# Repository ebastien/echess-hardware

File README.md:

# e-Chess project

Models for 3D printing and PCB layouts.

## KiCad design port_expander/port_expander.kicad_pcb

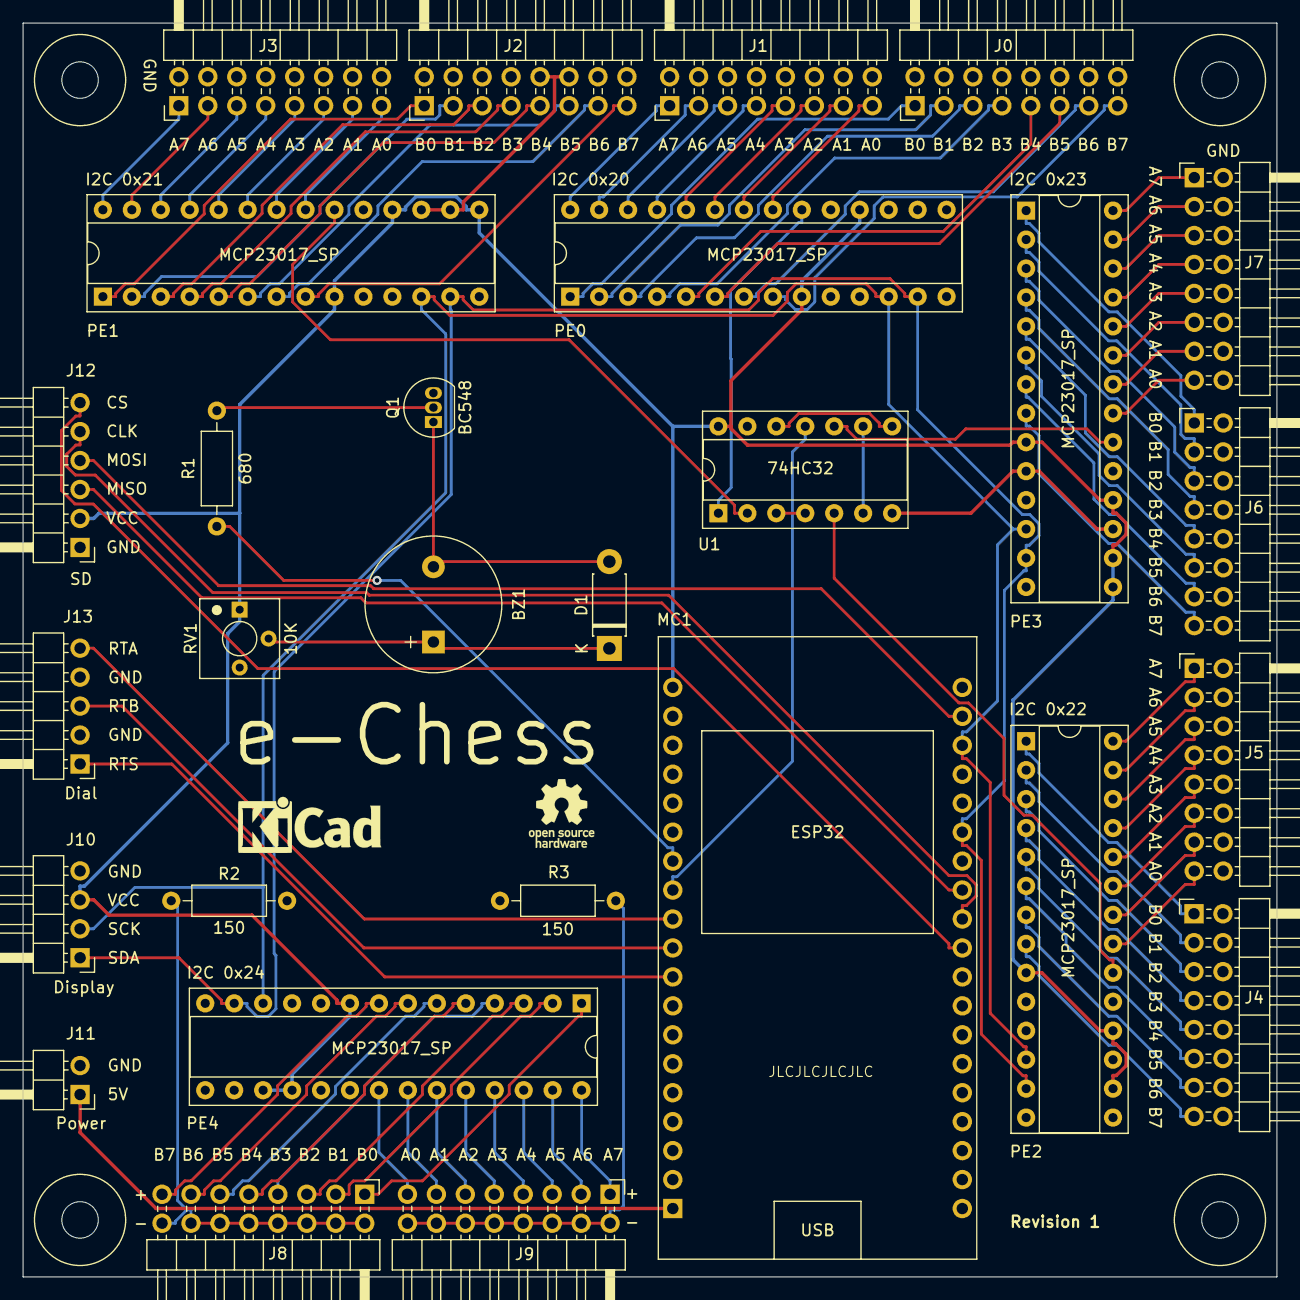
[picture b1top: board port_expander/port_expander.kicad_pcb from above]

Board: 2 copper layers, 110.0 x 110.0 mm, 33 parts (0 on the bottom side), 106 nets.

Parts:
BZ1: Buzzer; PassiveBuzzer_D12_H8.2_P6.6
D1: 1N4007; D_DO-41_SOD81_P7.62mm_Horizontal
J0, J1, J2, J3, J4, J5, J6, J7, J8, J9: Conn_02x08_Male; PinHeader_2x08_P2.54mm_Horizontal
J10: Display; PinHeader_1x04_P2.54mm_Horizontal
J11: Power; PinHeader_1x02_P2.54mm_Horizontal
J12: SD; PinHeader_1x06_P2.54mm_Horizontal
J13: Dial; PinHeader_1x05_P2.54mm_Horizontal
L0: KiCad-Logo_5mm_SilkScreen
MC1: ESP32_DevKitC
MH1, MH2, MH3, MH4: MountingHole_3.2mm_M3
PE0, PE1, PE2, PE3, PE4: MCP23017_SP; DIP-28_W7.62mm_Socket
Q1: BC548; TO-92_Inline
R1: 680; R_Axial_DIN0207_L6.3mm_D2.5mm_P10.16mm_Horizontal
R2, R3: 150; R_Axial_DIN0207_L6.3mm_D2.5mm_P10.16mm_Horizontal
RV1: 10K; BOURNS-3362P_pot
U1: 74HC32; DIP-14_W7.62mm_Socket

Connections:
+3V3: J10.3, J12.2, MC1.19, PE0.9, PE0.18, PE1.9, PE1.15, PE1.18, PE2.9, PE2.16, PE2.18, PE3.9, PE3.15, PE3.16, PE3.18, PE4.9, PE4.17, PE4.18, RV1.1, U1.14
/5V: J11.1, MC1.1
/BUZ: MC1.13, R1.2
/E0A0: J1.15, PE0.21
/E0A1: J1.13, PE0.22
/E0A2: J1.11, PE0.23
/E0A3: J1.9, PE0.24
/E0A4: J1.7, PE0.25
/E0A5: J1.5, PE0.26
/E0A6: J1.3, PE0.27
/E0A7: J1.1, PE0.28
/E0B0: J0.1, PE0.1
/E0B1: J0.3, PE0.2
/E0B2: J0.5, PE0.3
/E0B3: J0.7, PE0.4
/E0B4: J0.9, PE0.5
/E0B5: J0.11, PE0.6
/E0B6: J0.13, PE0.7
/E0B7: J0.15, PE0.8
/E1A0: J3.15, PE1.21
/E1A1: J3.13, PE1.22
/E1A2: J3.11, PE1.23
/E1A3: J3.9, PE1.24
/E1A4: J3.7, PE1.25
/E1A5: J3.5, PE1.26
/E1A6: J3.3, PE1.27
/E1A7: J3.1, PE1.28
/E1B0: J2.1, PE1.1
/E1B1: J2.3, PE1.2
/E1B2: J2.5, PE1.3
/E1B3: J2.7, PE1.4
/E1B4: J2.9, PE1.5
/E1B5: J2.11, PE1.6
/E1B6: J2.13, PE1.7
/E1B7: J2.15, PE1.8
/E2A0: J5.15, PE2.21
/E2A1: J5.13, PE2.22
/E2A2: J5.11, PE2.23
/E2A3: J5.9, PE2.24
/E2A4: J5.7, PE2.25
/E2A5: J5.5, PE2.26
/E2A6: J5.3, PE2.27
/E2A7: J5.1, PE2.28
/E2B0: J4.1, PE2.1
/E2B1: J4.3, PE2.2
/E2B2: J4.5, PE2.3
/E2B3: J4.7, PE2.4
/E2B4: J4.9, PE2.5
/E2B5: J4.11, PE2.6
/E2B6: J4.13, PE2.7
/E2B7: J4.15, PE2.8
/E3A0: J7.15, PE3.21
/E3A1: J7.13, PE3.22
/E3A2: J7.11, PE3.23
/E3A3: J7.9, PE3.24
/E3A4: J7.7, PE3.25
/E3A5: J7.5, PE3.26
/E3A6: J7.3, PE3.27
/E3A7: J7.1, PE3.28
/E3B0: J6.1, PE3.1
/E3B1: J6.3, PE3.2
/E3B2: J6.5, PE3.3
/E3B3: J6.7, PE3.4
/E3B4: J6.9, PE3.5
/E3B5: J6.11, PE3.6
/E3B6: J6.13, PE3.7
/E3B7: J6.15, PE3.8
/E4A0: J9.15, PE4.21
/E4A1: J9.13, PE4.22
/E4A2: J9.11, PE4.23
/E4A3: J9.9, PE4.24
/E4A4: J9.7, PE4.25
/E4A5: J9.5, PE4.26
/E4A6: J9.3, PE4.27
/E4A7: J9.1, PE4.28
/E4B0: J8.1, PE4.1
/E4B1: J8.3, PE4.2
/E4B2: J8.5, PE4.3
/E4B3: J8.7, PE4.4
/E4B4: J8.9, PE4.5
/E4B5: J8.11, PE4.6
/E4B6: J8.13, PE4.7
/E4B7: J8.15, PE4.8
/INT: MC1.12, U1.11
/INT0: PE0.20, U1.1
/INT1: PE1.20, U1.2
/INT2: PE2.20, U1.5
/INT3: PE3.20, U1.10
/MISO: J12.3, MC1.27
/MOSI: J12.4, MC1.21
/RTA: J13.5, MC1.11
/RTB: J13.3, MC1.10
/RTS: J13.1, MC1.9
/SCK: J10.2, MC1.22, PE0.12, PE1.12, PE2.12, PE3.12, PE4.12
/SDA: J10.1, MC1.25, PE0.13, PE1.13, PE2.13, PE3.13, PE4.13
/SPICLK: J12.5, MC1.28
/SPICS: J12.6, MC1.29
GND: J0.2, J0.4, J0.6, J0.8, J0.10, J0.12, J0.14, J0.16, J1.2, J1.4, J1.6, J1.8, J1.10, J1.12, J1.14, J1.16, J2.2, J2.4, J2.6, J2.8, J2.10, J2.12, J2.14, J2.16, J3.2, J3.4, J3.6, J3.8, J3.10, J3.12, J3.14, J3.16, J4.2, J4.4, J4.6, J4.8, J4.10, J4.12, J4.14, J4.16, J5.2, J5.4, J5.6, J5.8, J5.10, J5.12, J5.14, J5.16, J6.2, J6.4, J6.6, J6.8, J6.10, J6.12, J6.14, J6.16, J7.2, J7.4, J7.6, J7.8, J7.10, J7.12, J7.14, J7.16, J10.4, J11.2, J12.1, J13.2, J13.4, MC1.6, MC1.20, MC1.26, PE0.10, PE0.15, PE0.16, PE0.17, PE1.10, PE1.16, PE1.17, PE2.10, PE2.15, PE2.17, PE3.10, PE3.17, PE4.10, PE4.15, PE4.16, Q1.3, R2.2, R3.2, U1.7, U1.13
unnamed: BZ1.1, D1.1, RV1.2
unnamed: BZ1.2, D1.2, Q1.1
unnamed: J8.2, J8.4, J8.6, J8.8, J8.10, J8.12, J8.14, J8.16, R2.1
unnamed: J9.2, J9.4, J9.6, J9.8, J9.10, J9.12, J9.14, J9.16, R3.1
unnamed: Q1.2, R1.1
unnamed: U1.3, U1.4
unnamed: U1.6, U1.9
unnamed: U1.8, U1.12

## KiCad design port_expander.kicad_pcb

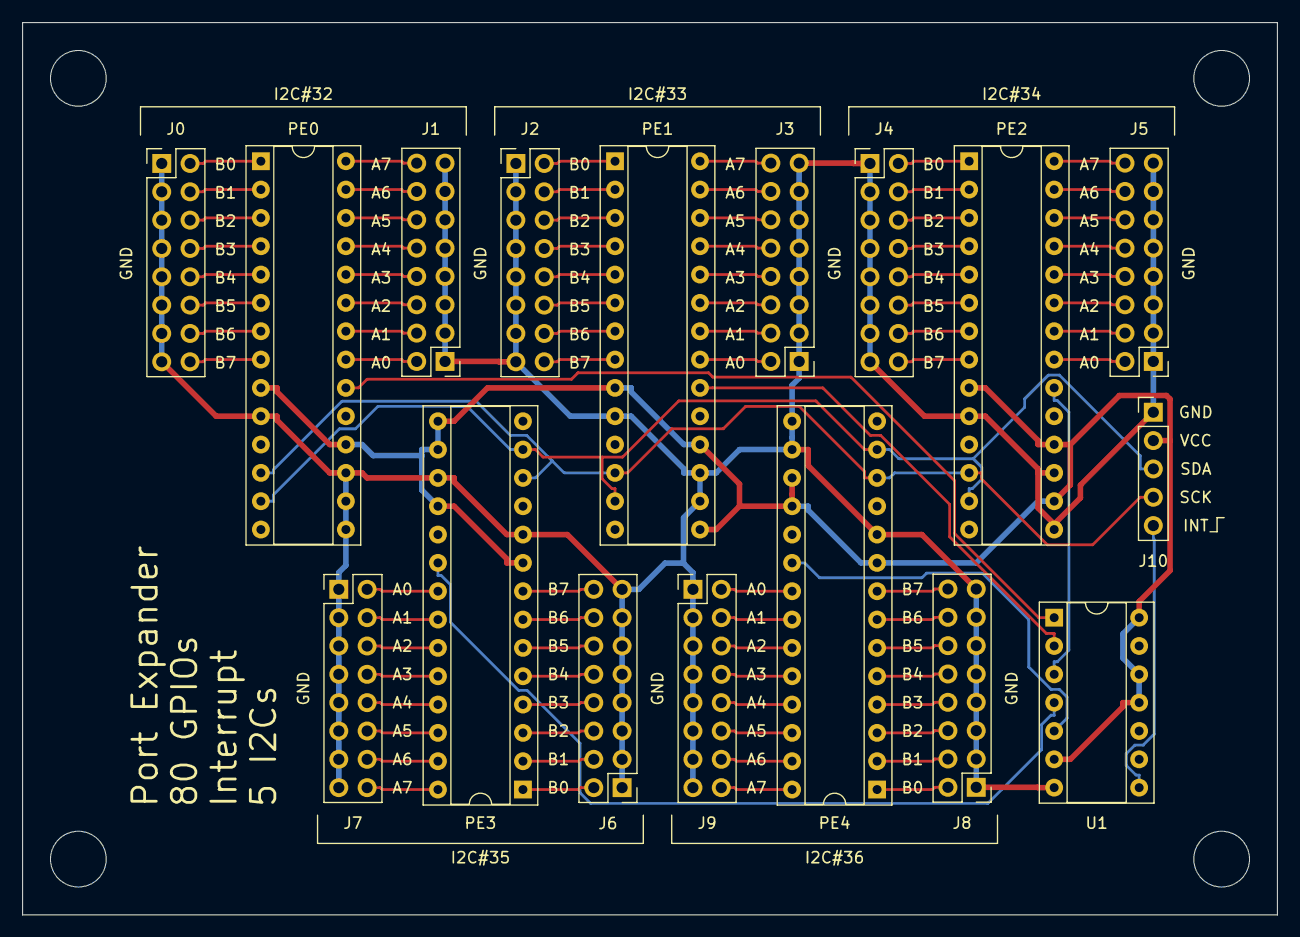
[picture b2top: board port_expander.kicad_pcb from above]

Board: 2 copper layers, 112.5 x 80.0 mm, 17 parts (0 on the bottom side), 90 nets.

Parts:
J0, J1, J2, J3, J4, J5, J6, J7, J8, J9: Conn_02x08_Male; PinHeader_2x08_P2.54mm_Vertical
J10: Conn_01x05_Male; PinHeader_1x05_P2.54mm_Vertical
PE0, PE1, PE2, PE3, PE4: MCP23017_SP; DIP-28_W7.62mm_Socket
U1: 74LS30; DIP-14_W7.62mm_Socket

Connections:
+3V3: J10.2, PE0.9, PE0.18, PE1.9, PE1.15, PE1.18, PE2.9, PE2.16, PE2.18, PE3.9, PE3.15, PE3.16, PE3.18, PE4.9, PE4.17, PE4.18, U1.6, U1.11, U1.12, U1.14
/INT: J10.5, U1.8
/INT0: PE0.20, U1.1
/INT1: PE1.20, U1.2
/INT2: PE2.20, U1.3
/INT3: PE3.20, U1.4
/INT4: PE4.20, U1.5
/SCK: J10.4, PE0.12, PE1.12, PE2.12, PE3.12, PE4.12
/SDA: J10.3, PE0.13, PE1.13, PE2.13, PE3.13, PE4.13
GND: J0.1, J0.3, J0.5, J0.7, J0.9, J0.11, J0.13, J0.15, J1.1, J1.3, J1.5, J1.7, J1.9, J1.11, J1.13, J1.15, J2.1, J2.3, J2.5, J2.7, J2.9, J2.11, J2.13, J2.15, J3.1, J3.3, J3.5, J3.7, J3.9, J3.11, J3.13, J3.15, J4.1, J4.3, J4.5, J4.7, J4.9, J4.11, J4.13, J4.15, J5.1, J5.3, J5.5, J5.7, J5.9, J5.11, J5.13, J5.15, J6.1, J6.3, J6.5, J6.7, J6.9, J6.11, J6.13, J6.15, J7.1, J7.3, J7.5, J7.7, J7.9, J7.11, J7.13, J7.15, J8.1, J8.3, J8.5, J8.7, J8.9, J8.11, J8.13, J8.15, J9.1, J9.3, J9.5, J9.7, J9.9, J9.11, J9.13, J9.15, J10.1, PE0.10, PE0.15, PE0.16, PE0.17, PE1.10, PE1.16, PE1.17, PE2.10, PE2.15, PE2.17, PE3.10, PE3.17, PE4.10, PE4.15, PE4.16, U1.7
unnamed: J0.2, PE0.1
unnamed: J0.4, PE0.2
unnamed: J0.6, PE0.3
unnamed: J0.8, PE0.4
unnamed: J0.10, PE0.5
unnamed: J0.12, PE0.6
unnamed: J0.14, PE0.7
unnamed: J0.16, PE0.8
unnamed: J1.2, PE0.21
unnamed: J1.4, PE0.22
unnamed: J1.6, PE0.23
unnamed: J1.8, PE0.24
unnamed: J1.10, PE0.25
unnamed: J1.12, PE0.26
unnamed: J1.14, PE0.27
unnamed: J1.16, PE0.28
unnamed: J2.2, PE1.1
unnamed: J2.4, PE1.2
unnamed: J2.6, PE1.3
unnamed: J2.8, PE1.4
unnamed: J2.10, PE1.5
unnamed: J2.12, PE1.6
unnamed: J2.14, PE1.7
unnamed: J2.16, PE1.8
unnamed: J3.2, PE1.21
unnamed: J3.4, PE1.22
unnamed: J3.6, PE1.23
unnamed: J3.8, PE1.24
unnamed: J3.10, PE1.25
unnamed: J3.12, PE1.26
unnamed: J3.14, PE1.27
unnamed: J3.16, PE1.28
unnamed: J4.2, PE2.1
unnamed: J4.4, PE2.2
unnamed: J4.6, PE2.3
unnamed: J4.8, PE2.4
unnamed: J4.10, PE2.5
unnamed: J4.12, PE2.6
unnamed: J4.14, PE2.7
unnamed: J4.16, PE2.8
unnamed: J5.2, PE2.21
unnamed: J5.4, PE2.22
unnamed: J5.6, PE2.23
unnamed: J5.8, PE2.24
unnamed: J5.10, PE2.25
unnamed: J5.12, PE2.26
unnamed: J5.14, PE2.27
unnamed: J5.16, PE2.28
unnamed: J6.2, PE3.1
unnamed: J6.4, PE3.2
unnamed: J6.6, PE3.3
unnamed: J6.8, PE3.4
unnamed: J6.10, PE3.5
unnamed: J6.12, PE3.6
unnamed: J6.14, PE3.7
unnamed: J6.16, PE3.8
unnamed: J7.2, PE3.21
unnamed: J7.4, PE3.22
unnamed: J7.6, PE3.23
unnamed: J7.8, PE3.24
unnamed: J7.10, PE3.25
unnamed: J7.12, PE3.26
unnamed: J7.14, PE3.27
unnamed: J7.16, PE3.28
unnamed: J8.2, PE4.1
unnamed: J8.4, PE4.2
unnamed: J8.6, PE4.3
unnamed: J8.8, PE4.4
unnamed: J8.10, PE4.5
unnamed: J8.12, PE4.6
unnamed: J8.14, PE4.7
unnamed: J8.16, PE4.8
unnamed: J9.2, PE4.21
unnamed: J9.4, PE4.22
unnamed: J9.6, PE4.23
unnamed: J9.8, PE4.24
unnamed: J9.10, PE4.25
unnamed: J9.12, PE4.26
unnamed: J9.14, PE4.27
unnamed: J9.16, PE4.28

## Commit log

2021-01-04 chore: first schematic iteration
2021-01-07 2x8 headers
2021-01-07 first pcb iteration
2021-01-08 smaller pcb
2021-01-09 esp32 library
2021-01-10 change files layout
2022-11-20 board sensor array
2022-11-20 spacer
2022-11-20 first spacer print and reed fix pcb order
2022-11-20 port expander with MCU
2022-11-20 compact port expander layout
2022-11-20 case and pcb
2022-11-20 complete main board
2022-11-20 main board routing
2022-11-20 refined routing
2022-11-20 pcb manufacturing
2022-11-20 display case
2022-11-20 diode on buzzer
2022-11-20 display and m3 spacer
2022-11-20 magnet holders and display improvement
2022-11-20 Add README.md
